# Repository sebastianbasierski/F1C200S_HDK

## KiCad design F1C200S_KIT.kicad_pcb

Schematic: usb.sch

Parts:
C31: 03.4001_C0603_1uF; C_0603_1608Metric
C33: 03.4002_C0603_2.2uF; C_0603_1608Metric
C34: 03.0009_C0402_100nF; C_0603_1608Metric
D2: SP0503BAHT; SOT-143
J2, J5: 10.0002_USB_Micro; USB_Micro-B_Amphenol_10103594-0001LF_Horizontal
R18: 02.0005_R0402_4K7_1%; R_0402_1005Metric
R20: 02.0008_R0402_10K_1%; R_0402_1005Metric
U4: 09.0001_CP2104; QFN-24-1EP_4x4mm_P0.5mm_EP2.6x2.6mm

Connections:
/CPU_RXD: U4.21 (TXD); also elsewhere on the board
/CPU_TXD: U4.20 (RXD); also elsewhere on the board
/USB_D+: D2.2 (K), J5.3 (D+); also elsewhere on the board
/USB_D-: D2.3 (K), J5.2 (D-); also elsewhere on the board
/USB_ID: D2.4 (K), J5.4 (ID), R20.2; also elsewhere on the board
/VBUS: C31.2, J2.1 (VBUS), J5.1 (VBUS), U4.7 (REGIN), U4.8 (VBUS); also elsewhere on the board
/usb/CP2104_RST: C33.2, C34.2, R18.2, U4.5 (VIO), U4.6 (VDD)
GND: C31.1, C33.1, C34.1, D2.1 (A), J2.5 (GND), J2.6 (Shield), J5.5 (GND), J5.6 (Shield), U4.2 (GND), U4.25 (PAD); also elsewhere on the board
unnamed: J2.2 (D-), U4.4 (D-)
unnamed: J2.3 (D+), U4.3 (D+)
unnamed: R18.1, U4.9 (~RST)

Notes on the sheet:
use USB2512: - one port for wifi - second port for further usage
Note: add tvs

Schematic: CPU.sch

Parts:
C1, C2, C5, C11, C12: 03.4004_C0603_10uF; C_0603_WJQ
C3, C4, C6, C7, C8, C9, C10, C13, C14, C15: 03.0009_C0402_100nF; C_0402_WJQ
C16: 03.0001_C0402_1uF; C_0402_WJQ
C17, C18: 03.0003_C0402_10pF; C_0402_WJQ
J1: 10.0402_LCD_RGB_CON_WJQ; FPC_40_0.5_BR
R1, R2: 02.0026_R0402_2K_1%; R_0402_WJQ
R3: 02.0008_R0402_10K_1%; R_0402_WJQ
SW1: 11.0101_SW-A03-08; SW_Push_Button__A03-08
TP1: TestPoint; TestPoint_Pad_1.0x1.0mm
U1: 08.0001_F1C200S; QFN-88_EP_10x10_Pitch0.4mm
Y1: 07.0403_Crystal_24M_3225; Crystal_SMD_3225-4Pin_3.2x2.5mm

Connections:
+1V2: C2.1, C4.1, C7.1, C10.1, U1.22 (VDD_CORE), U1.35 (VDD_CORE), U1.71 (VDD_CORE); also elsewhere on the board
+2V5: C11.1, C12.1, C13.1, C14.2, R1.2, U1.30 (VCC_DRAM), U1.31 (VCC_DRAM), U1.32 (VCC_DRAM), U1.34 (VCC_DRAM), U1.36 (VCC_DRAM); also elsewhere on the board
+5V: J1.39 (VCC5V), J1.40 (VCC5V); also elsewhere on the board
/CPU/CTP_INT: J1.2 (CTP_INT), U1.46 (PE3)
/CPU/CTP_RST: J1.6 (CTP_RST), U1.45 (PE4)
/CPU/LCD_BL: J1.7 (LCD_BL), U1.43 (PE6)
/CPU/LCD_CLK: J1.11 (SCK), U1.26 (PD18/LCD_CLK)
/CPU/LCD_D2: J1.18 (B2), U1.6 (PD0/LCD_D2)
/CPU/LCD_D3: J1.17 (B3), U1.7 (PD1/LCD_d3)
/CPU/LCD_D4: J1.16 (B4), U1.8 (PD2/LCD_D4)
/CPU/LCD_D5: J1.15 (B5), U1.9 (PD3/LCD_D5)
/CPU/LCD_D6: J1.14 (B6), U1.10 (PD4/LCD_D6)
/CPU/LCD_D7: J1.13 (B7), U1.11 (PD5/LCD_D7)
/CPU/LCD_D10: J1.27 (G2), U1.12 (PD6/LCD_D10)
/CPU/LCD_D11: J1.26 (G3), U1.13 (PD7/LCD_D11)
/CPU/LCD_D12: J1.25 (G4), U1.14 (PD8/LCD_D12)
/CPU/LCD_D13: J1.24 (G5), U1.15 (PD9/LCD_D13)
/CPU/LCD_D14: J1.23 (G6), U1.16 (PD10/LCD_D14)
/CPU/LCD_D15: J1.22 (G7), U1.17 (PD11/LCD_D15)
/CPU/LCD_D18: J1.36 (R2), U1.18 (PD12/LCD_D18)
/CPU/LCD_D19: J1.35 (R3), U1.19 (PD13/LCD_D19)
/CPU/LCD_D20: J1.34 (R4), U1.21 (PD14/LCD_D20)
/CPU/LCD_D21: J1.33 (R5), U1.23 (PD15/LCD_D21)
/CPU/LCD_D22: J1.32 (R6), U1.24 (PD16/LCD_D22)
/CPU/LCD_D23: J1.31 (R7), U1.25 (PD17/LCD_D23)
/CPU/LCD_DE: J1.8 (DE), U1.27 (PD19/LCD_DE)
/CPU/LCD_HS: J1.10 (HS), U1.28 (PD20/LCD_HSYNC)
/CPU/LCD_VS: J1.9 (VS), U1.29 (PD21/LCD_VSYNC)
/CPU/SOCI: C17.1, U1.51 (SOCI), Y1.1
/CPU/SOCO: C18.1, U1.52 (SOCO), Y1.3
/CPU_RXD: U1.49 (PE0); also elsewhere on the board
/CPU_TXD: U1.48 (PE1); also elsewhere on the board
/PA0_UART1_RTS_SPI1_CS: U1.66 (PA0); also elsewhere on the board
/PA1_UART1_CTS_SPI1_MOSI: U1.65 (PA1); also elsewhere on the board
/PA2_UART1_RX_SPI1_CLK: U1.64 (PA2); also elsewhere on the board
/PA3_UART1_TX_SPI1_MISO: U1.63 (PA3); also elsewhere on the board
/PE5: U1.44 (PE5); also elsewhere on the board
/PE7_UART2_TX_SPI1_CS: U1.42 (PE7); also elsewhere on the board
/PE8_UART2_RX_SPI1_MOSI: U1.41 (PE8); also elsewhere on the board
/PE9_UART2_RTS_SPI1_CLK: U1.40 (PE9); also elsewhere on the board
/PE10_UART2_CTS_SPI1_MISO: U1.39 (PE10); also elsewhere on the board
/PE11_TWI0_SCK: J1.3 (CTP_SCK), U1.38 (PE11); also elsewhere on the board
/PE12_TWI0_SDA: J1.5 (CTP_SDA), U1.37 (PE12/DA_MCLK/TWIO_SDA/PWM0); also elsewhere on the board
/SDIO_CLK: U1.56 (PF2); also elsewhere on the board
/SDIO_CMD: U1.55 (PF3); also elsewhere on the board
/SDIO_D0: U1.57 (PF1); also elsewhere on the board
/SDIO_D1: U1.58 (PF0); also elsewhere on the board
/SDIO_D2: U1.53 (PF5); also elsewhere on the board
/SDIO_D3: U1.54 (PF4); also elsewhere on the board
/SPI0_CLK: U1.59 (PC0); also elsewhere on the board
/SPI0_CS: U1.60 (PC1); also elsewhere on the board
/SPI0_MISO: U1.61 (PC2); also elsewhere on the board
/SPI0_MOSI: U1.62 (PC3); also elsewhere on the board
/USB_D+: U1.69 (USB+DP); also elsewhere on the board
/USB_D-: U1.68 (USB_DM); also elsewhere on the board
/USB_ID: U1.47 (PE2); also elsewhere on the board
GND: C1.2, C2.2, C3.2, C4.2, C6.2, C7.2, C9.2, C10.2, C11.2, C12.2, C13.2, C15.1, C16.2, C17.2, C18.2, J1.12 (GND), J1.19 (B1), J1.20 (B0), J1.21 (GND), J1.28 (G1), J1.29 (G0), J1.30 (GND), J1.37 (R1), J1.38 (R0), J1.MP (MountPin), R2.1, SW1.2, U1.89 (EPAD), Y1.2, Y1.4; also elsewhere on the board
GNDA: C5.2, C8.2, U1.74 (TV_GND), U1.82 (AGND); also elsewhere on the board
unnamed: C14.1, C15.2, R1.1, R2.2, U1.33 (SVREF)
unnamed: C16.1, R3.2, SW1.1, U1.70 (RESET)
unnamed: TP1.1, U1.73 (TV_VCC)
VDDA: U1.80 (AVCC); also elsewhere on the board

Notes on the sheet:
RST Button

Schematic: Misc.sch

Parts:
C36, C37: 03.0009_C0402_100nF; C_0402_WJQ
J3: 10.0001_Micro_SD_Card; microSD_HRO_TF_01A
J4: 10.0201_PH2X15_2D54_V; PinHeader_2x15_P2.54mm_Vertical
R13, R14, R15, R16, R17: 02.0014_R0402_47K_1%; R_0402_WJQ
R19: 02.0008_R0402_10K_1%; R_0402_WJQ
U5: 09.0303_GD5F1GQ4; WSON-8-1EP_8x6mm_P1.27mm_EP3.4x4.3mm
U6: 09.0302_W25Q128JVS; SOIC-8_5.23x5.23mm_P1.27mm

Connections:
+5V: J4.12, J4.14; also elsewhere on the board
/PA0_UART1_RTS_SPI1_CS: J4.1; also elsewhere on the board
/PA1_UART1_CTS_SPI1_MOSI: J4.6; also elsewhere on the board
/PA2_UART1_RX_SPI1_CLK: J4.9; also elsewhere on the board
/PA3_UART1_TX_SPI1_MISO: J4.10; also elsewhere on the board
/PE5: J4.5; also elsewhere on the board
/PE7_UART2_TX_SPI1_CS: J4.15; also elsewhere on the board
/PE8_UART2_RX_SPI1_MOSI: J4.22; also elsewhere on the board
/PE9_UART2_RTS_SPI1_CLK: J4.19; also elsewhere on the board
/PE10_UART2_CTS_SPI1_MISO: J4.17; also elsewhere on the board
/PE11_TWI0_SCK: J4.27; also elsewhere on the board
/PE12_TWI0_SDA: J4.28; also elsewhere on the board
/SDIO_CLK: J3.5 (CLK); also elsewhere on the board
/SDIO_CMD: J3.3 (CMD), R15.2; also elsewhere on the board
/SDIO_D0: J3.7 (DAT0), R14.2; also elsewhere on the board
/SDIO_D1: J3.8 (DAT1), R13.2; also elsewhere on the board
/SDIO_D2: J3.1 (DAT2), R17.2; also elsewhere on the board
/SDIO_D3: J3.2 (DAT3/CD), R16.2; also elsewhere on the board
/SPI0_CLK: J4.4, U5.6 (SCLK), U6.6 (CLK); also elsewhere on the board
/SPI0_CS: J4.11, R19.1, U5.1 (CS), U6.1 (~CS); also elsewhere on the board
/SPI0_MISO: J4.2, U5.2 (SO), U6.2 (DO(IO1)); also elsewhere on the board
/SPI0_MOSI: J4.3, U5.5 (SI), U6.5 (DI(IO0)); also elsewhere on the board
GND: C36.2, C37.2, J3.6 (VSS), J3.10 (SHIELD), J4.8, J4.13, J4.21, J4.23, J4.30, U5.4 (VSS), U5.9 (EP), U6.4 (GND); also elsewhere on the board

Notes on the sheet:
PCB edge
SPI NAND Flash
SPI NOR Flash
SD NAND/JTAG/WIFI/TF CARD

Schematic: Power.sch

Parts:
C19, C21, C22, C23, C27, C28, C29: 03.4004_C0603_10uF; C_0603_WJQ
C20, C24, C25, C26: 03.0009_C0402_100nF; C_0402_WJQ
C30: 04.0002_CP1210_47uF; CP_EIA-3528-21_Kemet-B
D1: 07.0201_LED_Red_0603; LED_0603_1608Metric
F1: 07.0004_Fuse_0805_500mA; Fuse_0805_2012Metric
H1, H2: MountingHole_Pad_M3; MP_HOLE_L4_M3
L1, L2, L3: 06.0102_L2520_2.2uH; L_1008_2520_WJQ
LOGO1: Logo_Open_Hardware_Small; KiCad-Logo2_6mm_SilkScreen
R4: 02.0003_R0402_1K_1%; R_0402_WJQ
R5: 02.0001_R0402_0R_1%; R_0402_WJQ
R6, R7, R8, R11: 02.0023_R0402_150K_1%; R_0402_WJQ
R9: 02.0025_R0402_680K_1%; R_0402_WJQ
R10: 02.0024_R0402_470K_1%; R_0402_WJQ
U2: 09.0103_XC6206; SOT-23
U3: 09.0102_EA3036; QFN-20_EP_3x3_Pitch0.4mm

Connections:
+1V2: C23.1, C26.1, L3.1, R11.2; also elsewhere on the board
+2V5: C22.1, C25.1, L2.1, R10.2; also elsewhere on the board
+5V: C27.1, C28.1, C29.1, C30.1, F1.1, U3.7 (VIN2), U3.8 (EN2), U3.9 (EN1), U3.10 (VIN1), U3.16 (VCC), U3.18 (EN3), U3.19 (VIN3); also elsewhere on the board
/VBUS: F1.2; also elsewhere on the board
GND: C21.2, C22.2, C23.2, C24.2, C25.2, C26.2, C27.2, C28.2, C29.2, C30.2, H1.1, H2.1, R4.2, R5.1, R6.1, R7.1, R8.1, U3.1 (GND), U3.4 (AGND), U3.5 (GND), U3.12 (GND), U3.13 (AGND), U3.15 (AGND), U3.17 (AGND), U3.21 (PAD); also elsewhere on the board
GNDA: C19.2, C20.2, R5.2, U2.1 (GND); also elsewhere on the board
unnamed: D1.1 (K), R4.1
unnamed: L1.2, U3.11 (SW1)
unnamed: L2.2, U3.6 (SW2)
unnamed: L3.2, U3.20 (SW3)
unnamed: R6.2, R9.1, U3.14 (FB1)
unnamed: R7.2, R10.1, U3.3 (FB2)
unnamed: R8.2, R11.1, U3.2 (FB3)
VDDA: C19.1, C20.1, U2.2 (VO); also elsewhere on the board

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
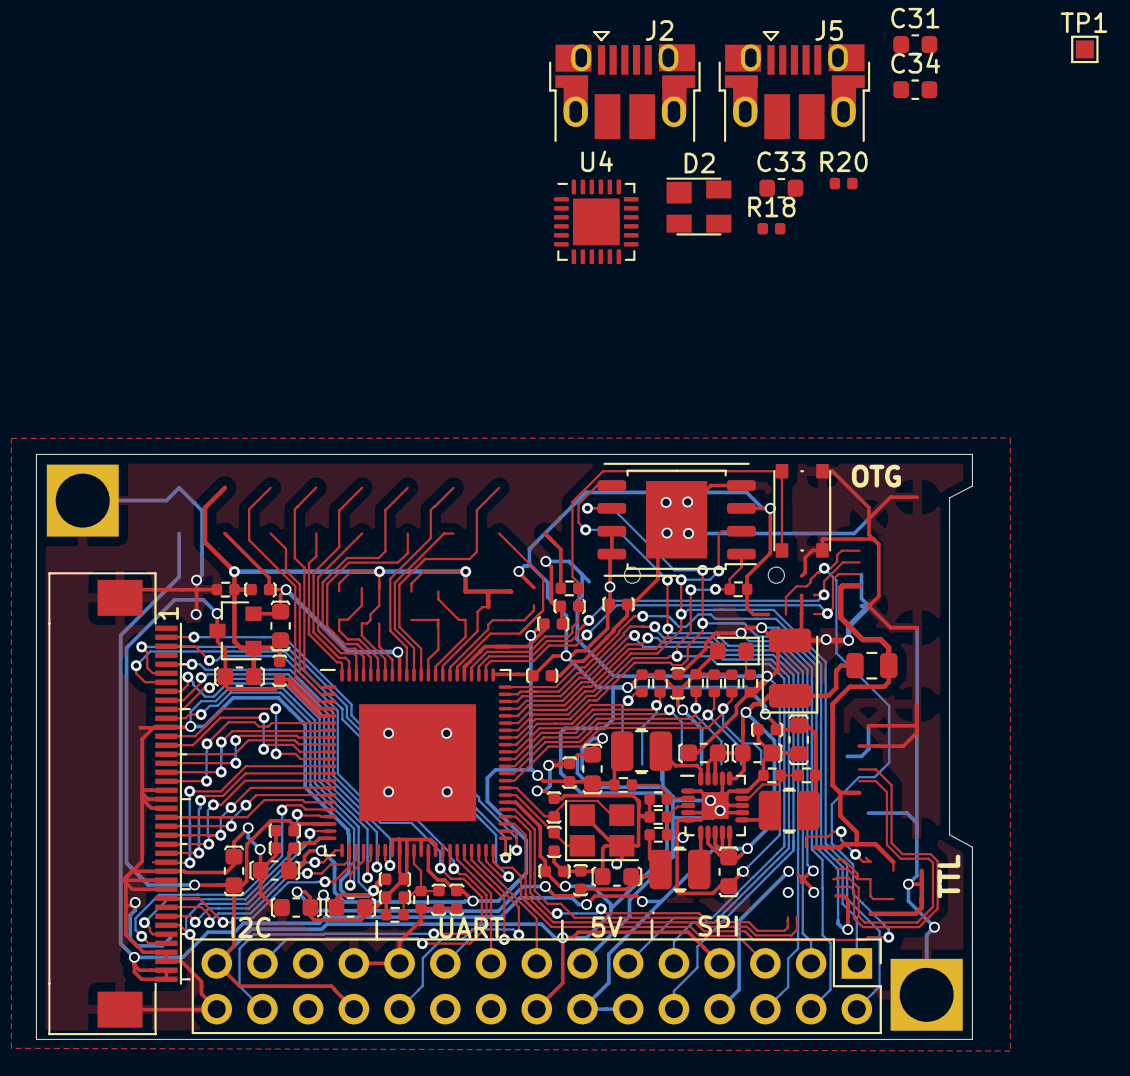
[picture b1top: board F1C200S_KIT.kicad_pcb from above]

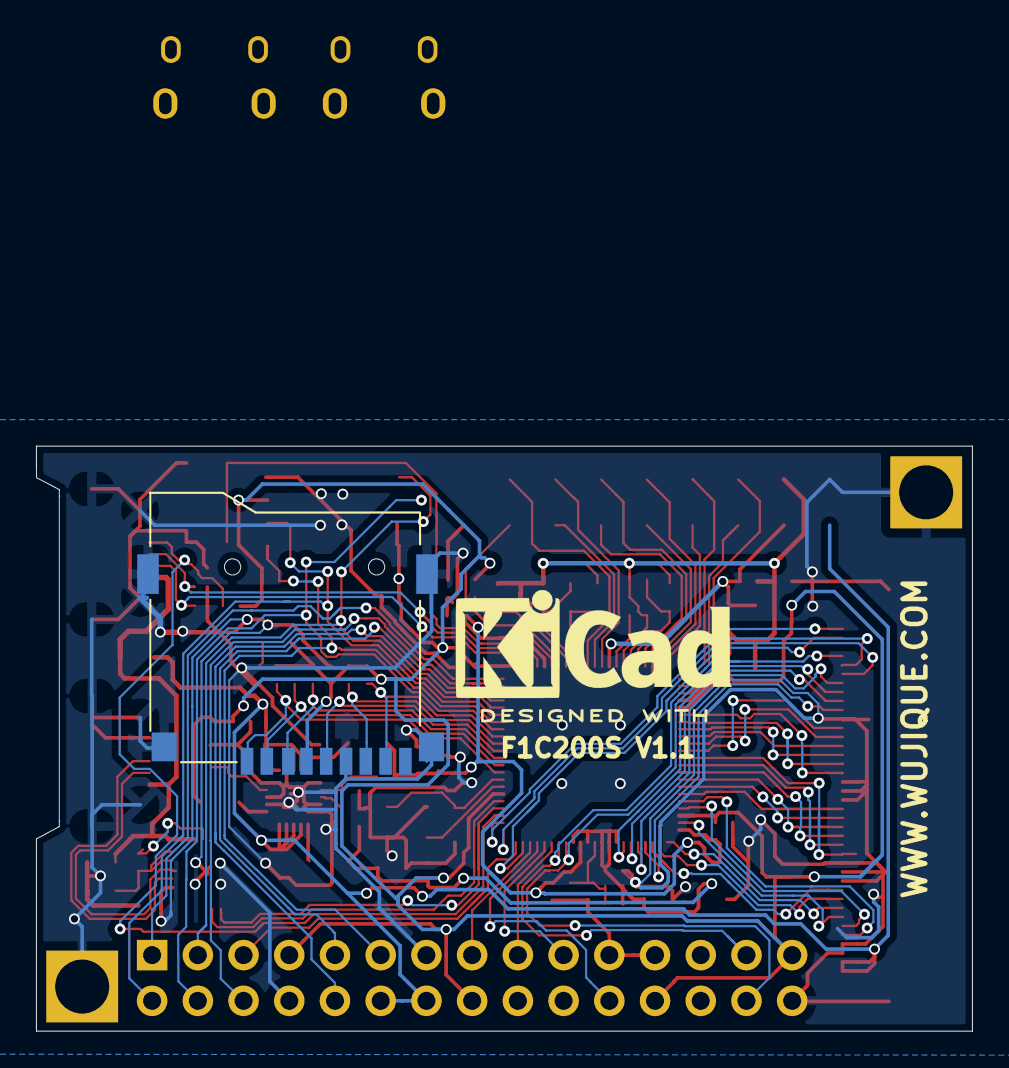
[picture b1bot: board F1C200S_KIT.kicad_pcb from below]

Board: 2 copper layers, 52.0 x 32.5 mm, 77 parts (2 on the bottom side), 75 nets.

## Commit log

2020-07-23 Removed TV. Added USB. Refactored.
